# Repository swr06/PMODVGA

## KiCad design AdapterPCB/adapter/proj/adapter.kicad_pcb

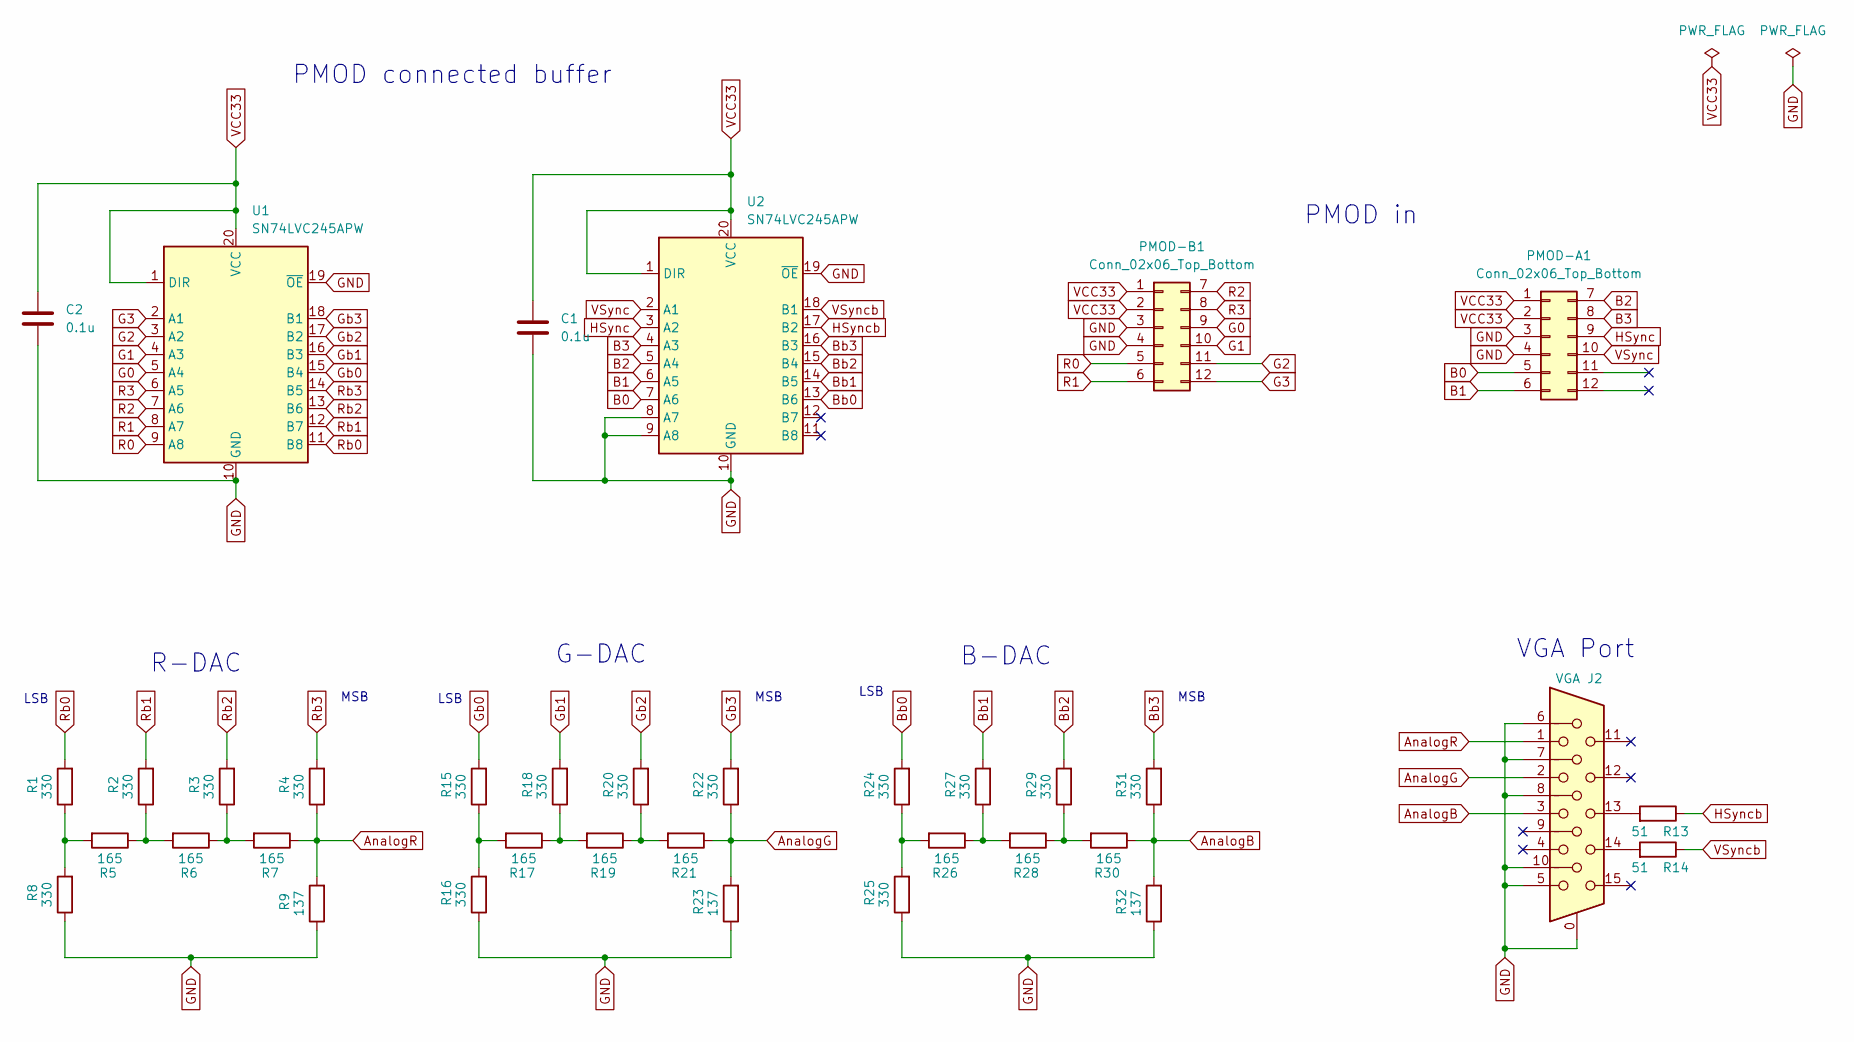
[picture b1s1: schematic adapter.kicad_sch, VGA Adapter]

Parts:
C1, C2: 0.1u; C_1206_3216Metric_Pad1.33x1.80mm_HandSolder
J2: VGA; DSUB-15-HD_Socket_Horizontal_P2.29x2.54mm_EdgePinOffset8.35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; MPN L77HDE15SD1CH4FVGA; LCSC C138387
PMOD-A1: Conn_02x06_Top_Bottom; PinHeader_2x06_P2.54mm_Horizontal
PMOD-B1: Conn_02x06_Top_Bottom; PinHeader_2x06_P2.54mm_Horizontal
R1, R2, R3, R4, R8, R15, R16, R18, R20, R22, R24, R25, R27, R29, R31: 330; R_1206_3216Metric_Pad1.30x1.75mm_HandSolder
R5, R6, R7, R17, R19, R21, R26, R28, R30: 165; R_1206_3216Metric_Pad1.30x1.75mm_HandSolder
R9, R23, R32: 137; R_1206_3216Metric_Pad1.30x1.75mm_HandSolder
R13, R14: 51; R_1206_3216Metric_Pad1.30x1.75mm_HandSolder; MPN ERJ-2RKF49R9X; LCSC C25120
U1, U2: SN74LVC245APW; SOIC-20W_7.5x12.8mm_P1.27mm

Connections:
AnalogB: J2.3, R30.1, R31.1, R32.2
AnalogG: J2.2, R21.1, R22.1, R23.2
AnalogR: J2.1, R4.1, R7.1, R9.2
B0: PMOD-A1.5, U2.7 (A6)
B1: PMOD-A1.6, U2.6 (A5)
B2: PMOD-A1.7, U2.5 (A4)
B3: PMOD-A1.8, U2.4 (A3)
Bb0: R24.2, U2.13 (B6)
Bb1: R27.2, U2.14 (B5)
Bb2: R29.2, U2.15 (B4)
Bb3: R31.2, U2.16 (B3)
G0: PMOD-B1.9, U1.5 (A4)
G1: PMOD-B1.10, U1.4 (A3)
G2: PMOD-B1.11, U1.3 (A2)
G3: PMOD-B1.12, U1.2 (A1)
GND: C1.2, C2.2, J2.0, J2.5, J2.6, J2.7, J2.8, J2.10, PMOD-A1.3, PMOD-A1.4, PMOD-B1.3, PMOD-B1.4, R8.1, R9.1, R16.1, R23.1, R25.1, R32.1, U1.10 (GND), U1.19 (~OE), U2.8 (A7), U2.9 (A8), U2.10 (GND), U2.19 (~OE)
Gb0: R15.2, U1.15 (B4)
Gb1: R18.2, U1.16 (B3)
Gb2: R20.2, U1.17 (B2)
Gb3: R22.2, U1.18 (B1)
HSync: PMOD-A1.9, U2.3 (A2)
HSyncb: R13.1, U2.17 (B2)
unnamed: J2.13, R13.2
unnamed: J2.14, R14.2
unnamed: R1.1, R5.2, R8.2
unnamed: R2.1, R5.1, R6.2
unnamed: R3.1, R6.1, R7.2
unnamed: R15.1, R16.2, R17.2
unnamed: R17.1, R18.1, R19.2
unnamed: R19.1, R20.1, R21.2
unnamed: R24.1, R25.2, R26.2
unnamed: R26.1, R27.1, R28.2
unnamed: R28.1, R29.1, R30.2
R0: PMOD-B1.5, U1.9 (A8)
R1: PMOD-B1.6, U1.8 (A7)
R2: PMOD-B1.7, U1.7 (A6)
R3: PMOD-B1.8, U1.6 (A5)
Rb0: R1.2, U1.11 (B8)
Rb1: R2.2, U1.12 (B7)
Rb2: R3.2, U1.13 (B6)
Rb3: R4.2, U1.14 (B5)
VCC33: C1.1, C2.1, PMOD-A1.1, PMOD-A1.2, PMOD-B1.1, PMOD-B1.2, U1.1 (DIR), U1.20 (VCC), U2.1 (DIR), U2.20 (VCC)
VSync: PMOD-A1.10, U2.2 (A1)
VSyncb: R14.1, U2.18 (B1)

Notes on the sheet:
LSB
VGA Port
B-DAC
PMOD in
MSB
PMOD connected buffer
R-DAC
G-DAC

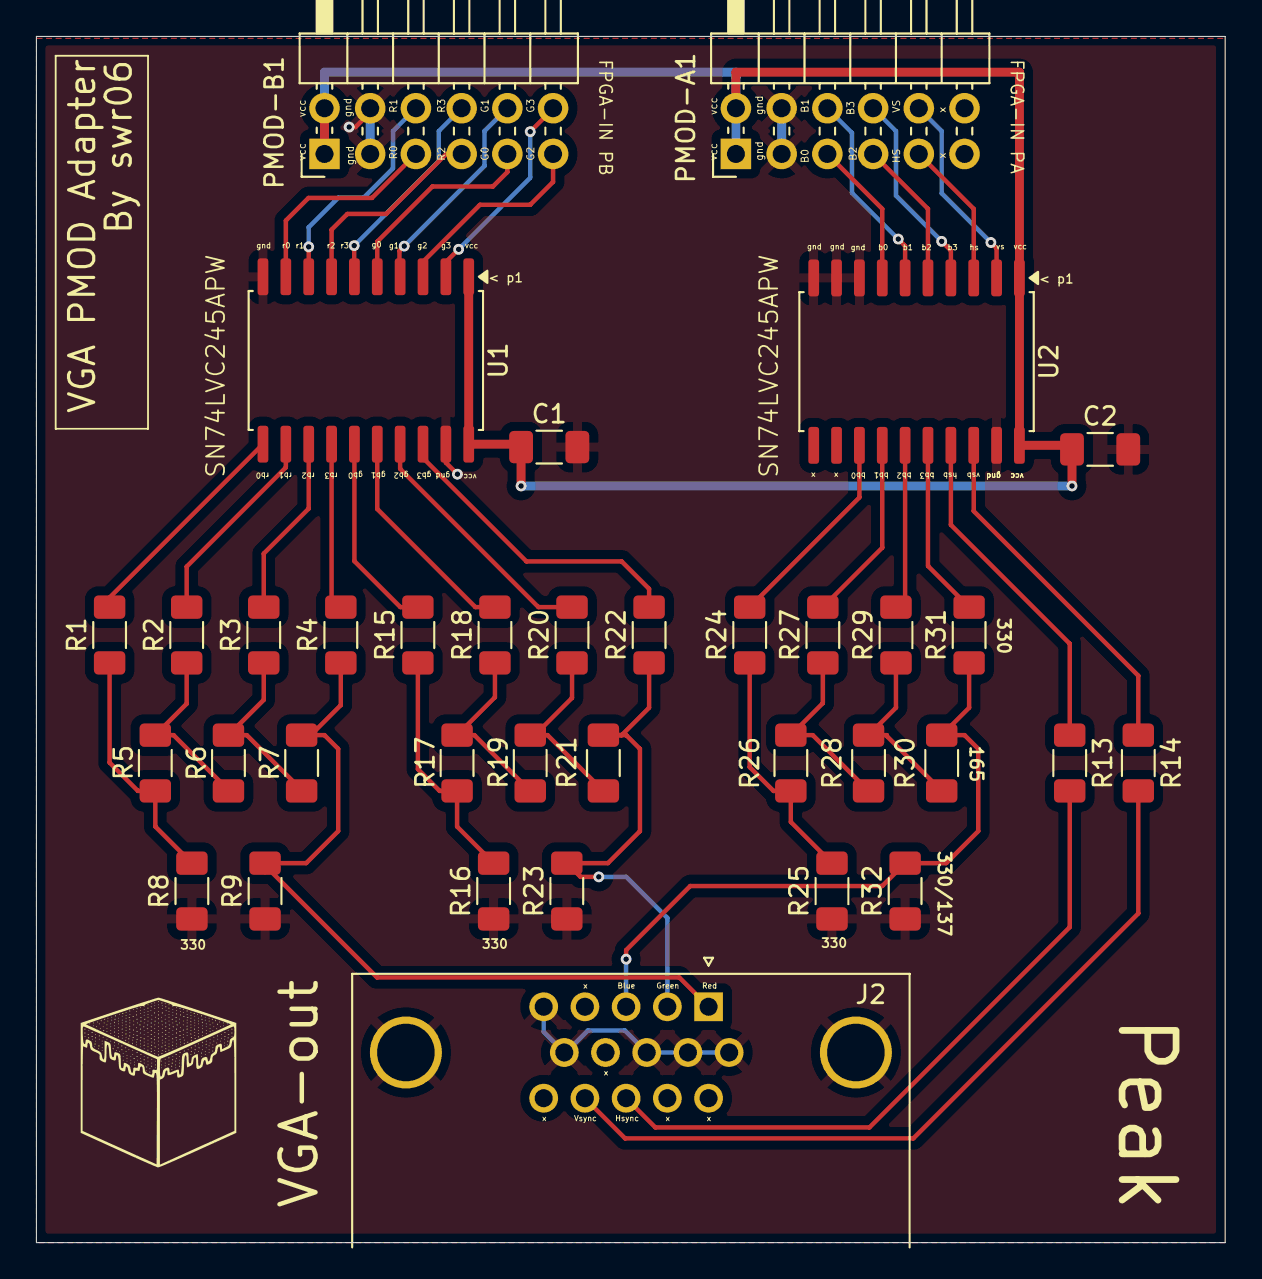
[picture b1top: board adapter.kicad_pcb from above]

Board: 2 copper layers, 66.0 x 67.0 mm, 36 parts (0 on the bottom side), 44 nets.

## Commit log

2026-02-05 work
2026-05-28 fixed drc
2026-05-28 added gerber
2026-05-28 yeyer
